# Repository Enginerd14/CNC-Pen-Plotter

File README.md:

# CNC-Pen-Plotter
A Computer Numerical Controlled machine that translates G-code to drawings on paper by moving a pen along the X and y axes

## Why I chose this project?
I chose to build a CNC pen plotter because it combines electronics and mechanical movement while also helping me develop my PCB and CAD design.

## How to use this project
You could you this for virtually any drawing whether thats to do your homework or to create some artwork. In the future, I am also thinking of upgrading it to amke a router or milling machine. 

## Schematic

## PCB

## PCB 3D render

## 3D Model

## Bill of Materials

| Item | Qty (Project) | Qty (Packs) | Price (£) | Link |
|------|---------------|------------|-----------|------|
| 600mm Aluminium extrusion | 3 | 1 | 32.05 | [Al extrusion 600mm 4pcs](https://www.aliexpress.com/item/1005003428294239.html) |
| V Wheels | 12 | 1 | 10.34 | [V Wheels set 24pcs](https://www.aliexpress.com/item/1005004275676552.html) |
| Limit Switches | 4 | 1 | 1.48 | [Limit Switches 5pcs](https://www.aliexpress.com/item/1005001834200980.html) |
| NEMA 17 | 2 | 1 | 17.99 | [NEMA 17](https://www.ebay.co.uk/itm/204595546364) |
| Timing Belt 6mm (5m) | 5m | 1 | 4.07 | [Timing belt 6mm](https://www.aliexpress.com/item/32921042288.html) |
| Belt Pulley | 2 | 1 | 4.99 | [Belt Pulley](https://www.aliexpress.com/item/1005010636842055.html) |
| Belt Idler | 2 | 1 | 3.85 | [Idler Pulley](https://www.aliexpress.com/item/1005008093251681.html) |
| ESP32 30pin Devkit v1 | 1 | 1 | 3.86 | [ESP32 Devkit](https://www.aliexpress.com/item/1005006140560853.html) |
| A4988 Motor Driver | 2 | 2 | 2.42 | [A4988](https://www.ebay.co.uk/itm/226914936307) |
| JST 3-pin connectors | 2 | 1 | 1.02 | [JST XH 3 pin 10pcs](https://www.aliexpress.com/item/1005007080333485.html) |
| JST 4-pin connectors | 2 | 1 | 1.23 | [JST XH 4 pin 10pcs](https://www.aliexpress.com/item/1005007080333485.html) |
| JST wire connectors | 2 | 1 | 1.31 | [JST wire connectors](https://www.aliexpress.com/item/1005007277110532.html) |
| Pin sockets (40pin breakaway) | 4 | 1 | 1.82 | [40pin socket 10pcs](https://www.aliexpress.com/item/4001198421663.html) |
| DC barrel jack 5.5mm/2.1mm | 1 | 1 | 0.74 | [DC barrel jack 10pcs](https://www.aliexpress.com/item/1005006827429781.html) |
| 7805 5V regulator | 1 | 1 | 1.36 | [7805 5V](https://www.ebay.co.uk/itm/388949401602) |
| 100µF capacitor | 3 | 1 | 3.39 | [100µF capacitor](https://www.ebay.co.uk/itm/303398108239) |
| 1µF capacitor | 1 | 1 | 1.89 | [1µF capacitor](https://www.ebay.co.uk/itm/355588015874) |
| Pin header breakaway | 10 | 1 | 3.39 | [Breakable pin header](https://www.aliexpress.com/item/1005007564228387.html) |
| 12V 3A power supply | 1 | 1 | 4.51 | [12V 3A power supply](https://www.aliexpress.com/item/4000494270389.html) |
| Servo SG90 | 1 | 1 | 1.23 | [SG90 Servo](https://www.aliexpress.com/item/1005006501322490.html) |
| 5mm(D) 45mm(L) Shaft | 2 | 1 | 2.59 | [5mm/45mm Shaft](https://www.aliexpress.com/item/1005007023343232.html) |
| 10mm Spring (ID 5mm) | 2 | 1 | 0.94 | [10mm spring 5pcs](https://www.aliexpress.com/item/1005010303542920.html) |
| 6mm Spacer M5 | 25 | 3D print | - | Spacer 10pcs |
| M5 Sliding Nuts | 12 | 1 | 1.40 | [Sliding nuts M5 20pcs](https://www.aliexpress.com/item/1005004658668930.html) |
| M5 Bolts | 30 | 1 | 9.54 | [M5 bolts 242pcs](https://www.aliexpress.com/item/1005007197683325.html) |
| M5 40mm Bolts (connecting plates) | 12 | 1 | 2.45 | [M5 40mm 20pcs](https://www.ebay.co.uk/itm/266129484527) |
| M3 4mm (for NEMA 17) | 8 | 1 | 1.15 | [M3 4mm 50pcs](https://www.aliexpress.com/item/4000970993800.html) |
| M5 Nyloc nuts | 30 | 1 | 3.34 | [M5 Nyloc nuts](https://www.aliexpress.com/item/32798773566.html) |
| Multistrand wire | 2m | 1 | 1.25 | [Multistrand wire](https://www.aliexpress.com/item/1005007251965003.html) |
| Cable spiral wrap | - | 1 | 3.32 | [Cable spiral wrap](https://www.aliexpress.com/item/1005003478796768.html) |
| 3D prints delivery | - | - | 10.00 | - |
| PCB cost | - | - | 5.00 | - |
| **TOTAL** |  |  | **£143.92 (~$196.38)** |  |

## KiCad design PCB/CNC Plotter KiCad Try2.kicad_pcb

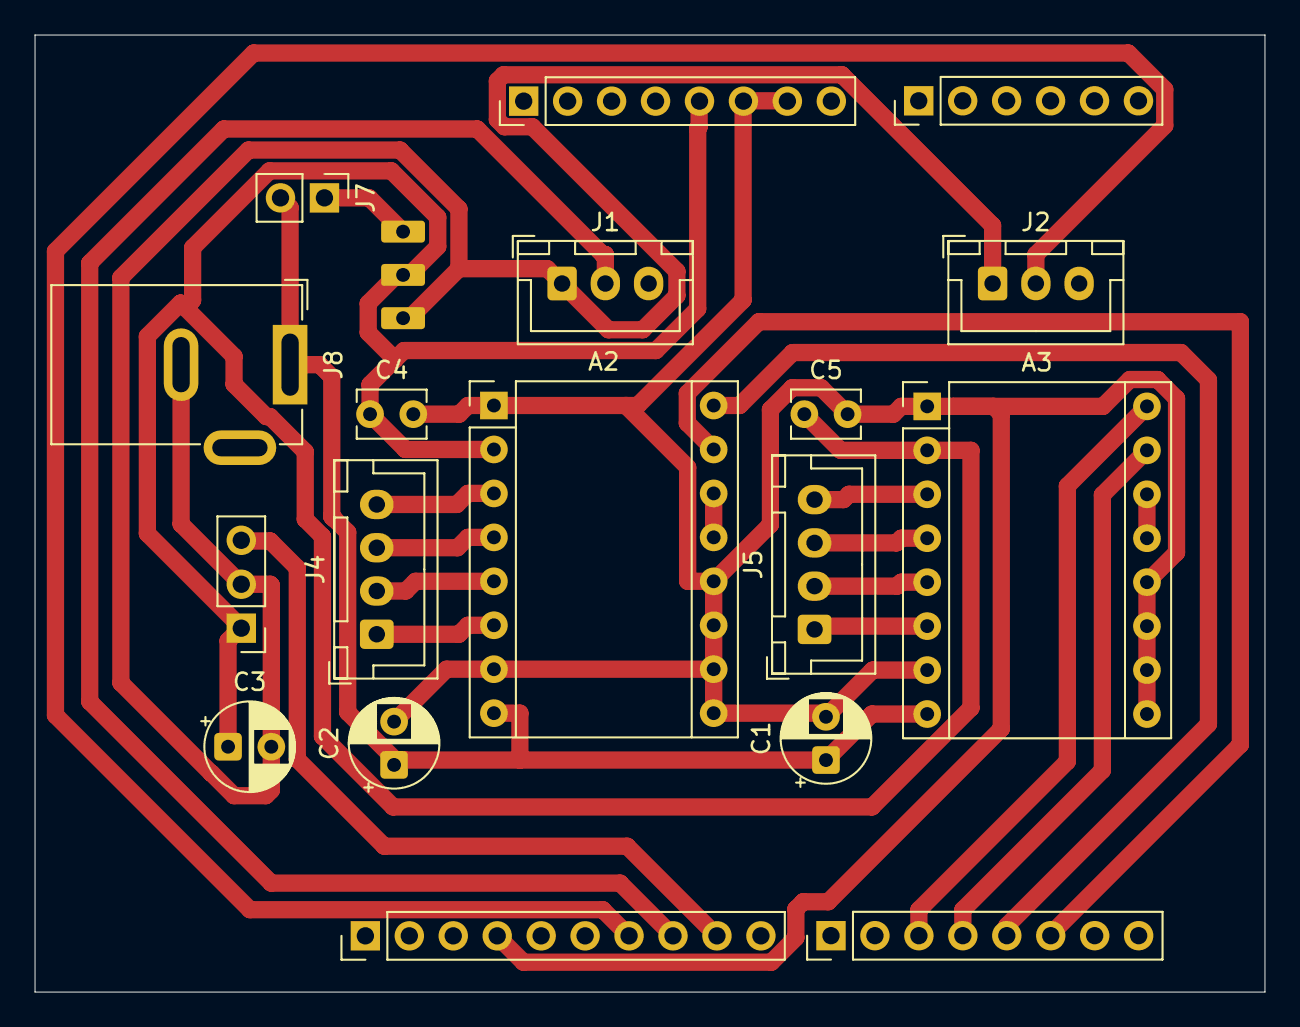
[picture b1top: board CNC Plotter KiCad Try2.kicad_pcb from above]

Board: 2 copper layers, 71.1 x 55.3 mm, 14 parts (0 on the bottom side), 15 nets.

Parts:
A2, A3: Pololu_Breakout_A4988; Pololu_Breakout-16_15.2x20.3mm
C1, C3: 100microfarads; CP_Radial_D5.0mm_P2.50mm
C2: 100microfards; CP_Radial_D5.0mm_P2.50mm
C4: 0.1microfards; C_Disc_D3.8mm_W2.6mm_P2.50mm
C5: 0.1microfarads; C_Disc_D3.8mm_W2.6mm_P2.50mm
J1: X-axis Limit Switch; JST_XH_B3B-XH-A_1x03_P2.50mm_Vertical
J2: Y-axis Limit Switch; JST_XH_B3B-XH-A_1x03_P2.50mm_Vertical
J4: X-axis NEMA 17; JST_XH_B4B-XH-A_1x04_P2.50mm_Vertical
J5: Y-axis NEMA 17; JST_XH_B4B-XH-A_1x04_P2.50mm_Vertical
J7: AdjBuck jumper; PinHeader_1x02_P2.54mm_Vertical
J8: Barrel_Jack; BarrelJack_GCT_DCJ200-10-A_Horizontal
LM2596Module2: LM2596 Module 5V adj; Untitled

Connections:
unnamed: A2.2 (VDD), A3.2 (VDD), C3.1, C4.1, C5.1, LM2596Module2.2 (VOUT)
unnamed: A2.4 (1A), J4.3
unnamed: A2.3 (1B), J4.4
unnamed: A2.5 (2A), J4.2
unnamed: A2.6 (2B), J4.1
unnamed: A2.1 (GND), A2.7 (GND), A2.9 (~ENABLE), A2.10 (MS1), A2.11 (MS2), A2.12 (MS3), A3.1 (GND), A3.7 (GND), A3.9 (~ENABLE), A3.10 (MS1), A3.11 (MS2), A3.12 (MS3), C1.2, C2.2, C4.2, C5.2
unnamed: A2.8 (VMOT), A3.8 (VMOT), C1.1, C2.1, J7.2, J8.1
unnamed: A2.13 (~RESET), A2.14 (~SLEEP)
unnamed: A3.4 (1A), J5.3
unnamed: A3.3 (1B), J5.4
unnamed: A3.5 (2A), J5.2
unnamed: A3.6 (2B), J5.1
unnamed: A3.13 (~RESET), A3.14 (~SLEEP)
unnamed: C3.2, J1.1, J2.1, J8.2, LM2596Module2.3 (GND)
unnamed: J7.1, LM2596Module2.1 (VIN)

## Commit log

2025-12-10 Create Cad
2025-12-10 Create PCB
2025-12-10 Create Firmware
2025-12-14 Document assembly process and update hours in JOURNAL.md
    Added images and details about the assembly process for the X-axis and Y-axis in Solidworks. Updated hours spent on the project.
2025-12-14 Enhance journal entries with design details and updates
    Updated the journal with additional details about the design process, including the use of 3D models for components and the assembly of the project. Added new entries for the dates 12/12/25, 13/12/25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
2025-12-21 Add images to README for PCB and 3D Model sections
2025-12-21 Document GRBL setup and power supply details
    Added notes on GRBL compatibility and power supply considerations for motors.
2025-12-21 Update README with schematic, PCB, and 3D model images
2025-12-21 Add PCB cost entry to README
    Added PCB cost entry to the cost table.
2025-12-21 Revise project motivation in README
    Updated the project motivation to include PCB and CAD design.
2025-12-21 Refine journal entry for 09/12/25
    Updated the journal entry for 09/12/25, correcting the hours spent and refining the design description.
2026-01-23 Add PCB and shipping costs to README
2026-01-23 Document feedback and PCB redesign with ESP32
    Added journal entry for project feedback and PCB remake.
2026-01-23 Revise journal entry for PCB redesign and updates
    Updated journal entry with new project details and images.
2026-01-23 Add firmware test script for motor control
2026-01-23 Update journal entry
    Added a note about testing functions before updating documentation.
2026-02-14 Update Bill of Materials section in README
2026-02-14 Enhance README with PCB render and model images
    Added PCB 3D render images and updated 3D model section.
2026-02-14 Update README.md
    Added a section about the project's schematic.
